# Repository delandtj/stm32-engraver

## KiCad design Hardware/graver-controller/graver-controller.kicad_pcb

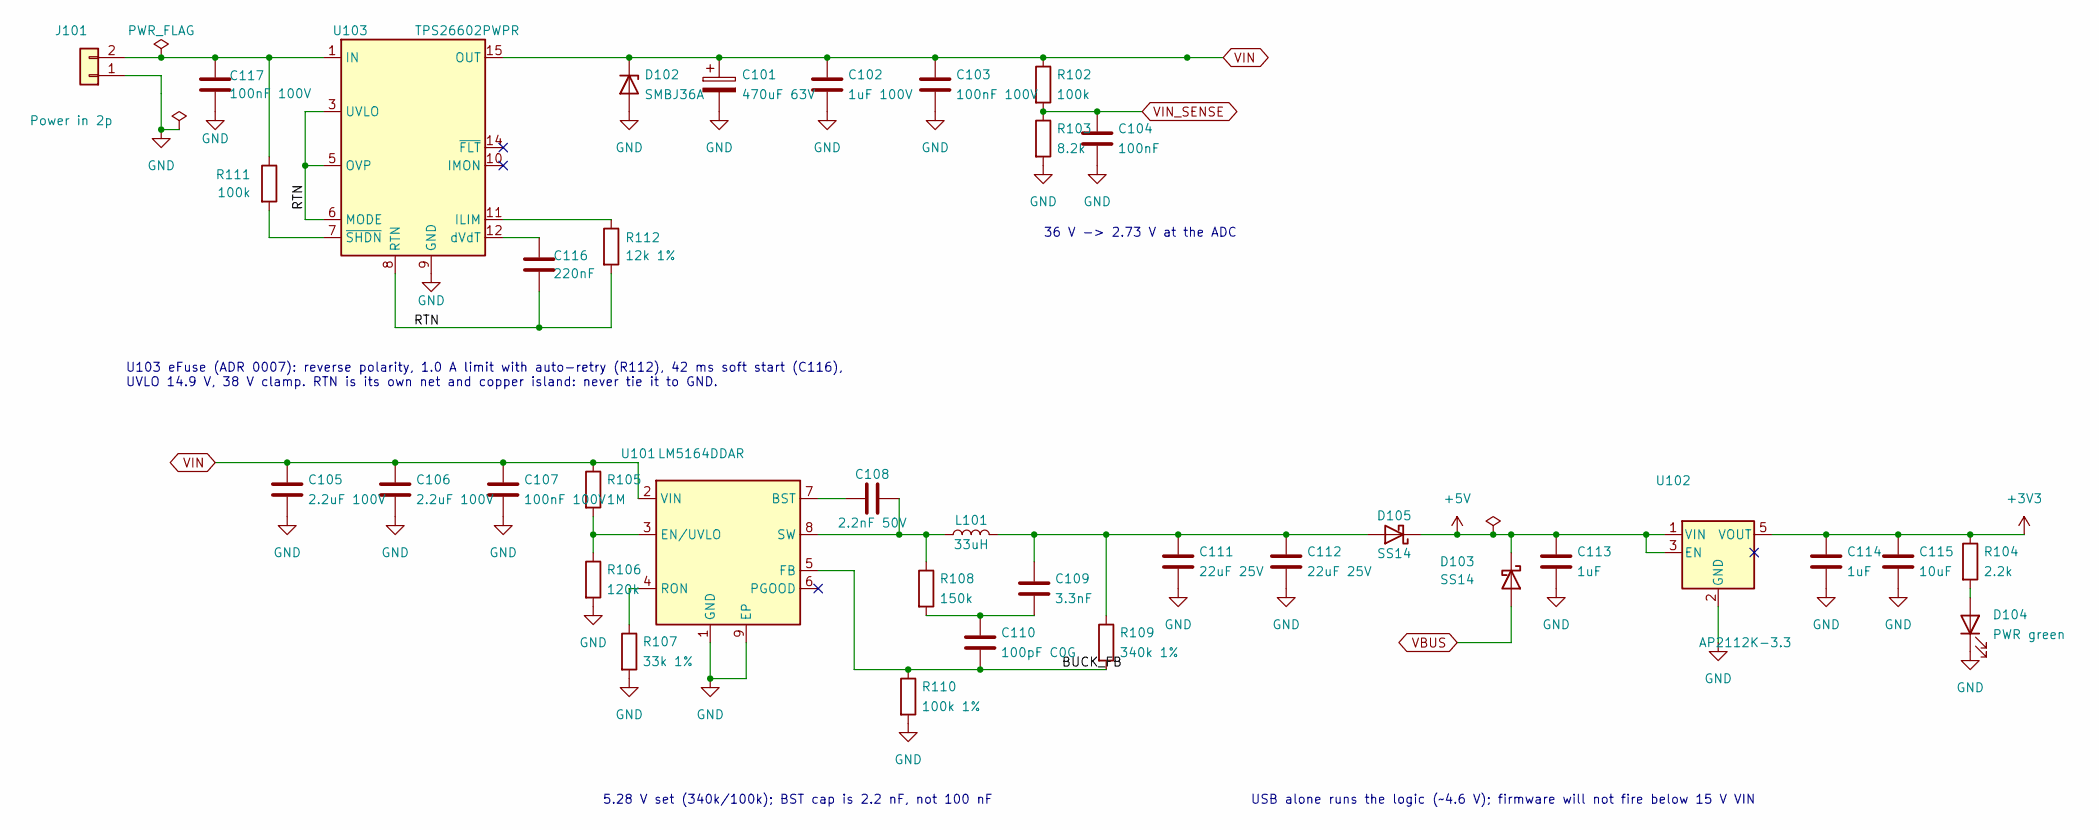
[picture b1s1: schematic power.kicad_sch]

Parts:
C101: 470uF 63V; CP_Radial_D12.5mm_P5.00mm; MPN 63ZLJ470M12.5X20; LCSC C2940725
C102: 1uF 100V; C_0805_2012Metric; MPN CC0805KKX7R0BB105; LCSC C5370002
C103, C107, C117: 100nF 100V; C_0805_2012Metric; MPN CL21B104KCFNNNE; LCSC C28233
C104: 100nF; C_0603_1608Metric; MPN CC0603KRX7R9BB104; LCSC C14663
C105, C106: 2.2uF 100V; C_1206_3216Metric; MPN CL31B225KCHSNNE; LCSC C170101
C108: 2.2nF 50V; C_0603_1608Metric; MPN CL10B222KB8NNNC; LCSC C1604
C109: 3.3nF; C_0603_1608Metric; MPN CL10B332KB8NNNC; LCSC C1613
C110: 100pF C0G; C_0603_1608Metric; MPN CL10C101JB8NNNC; LCSC C14858
C111, C112: 22uF 25V; C_0805_2012Metric; MPN CL21A226MAQNNNE; LCSC C45783
C113, C114: 1uF; C_0603_1608Metric; MPN CL10A105KB8NNNC; LCSC C15849
C115: 10uF; C_0805_2012Metric; MPN CL21A106KAYNNNE; LCSC C15850
C116: 220nF; C_0603_1608Metric; MPN CL10B224KA8NNNC; LCSC C21120
D102: SMBJ36A; D_SMB; MPN SMBJ36A; LCSC C19077588
D103, D105: SS14; D_SMA; MPN SS14; LCSC C2480
D104: PWR green; LED_0805_2012Metric; MPN KT-0805G; LCSC C2297
J101: Power in 2p; SolderWire-1sqmm_1x02_P5.4mm_D1.4mm_OD2.7mm
L101: 33uH; L_Changjiang_FXL0630; MPN FXL0630-330-M; LCSC C177245
R102, R111: 100k; R_0603_1608Metric; MPN 0603WAF1003T5E; LCSC C25803
R103: 8.2k; R_0603_1608Metric; MPN 0603WAF8201T5E; LCSC C25981
R104: 2.2k; R_0603_1608Metric; MPN 0603WAF2201T5E; LCSC C4190
R105: 1M; R_0603_1608Metric; MPN 0603WAF1004T5E; LCSC C22935
R106: 120k; R_0603_1608Metric; MPN 0603WAF1203T5E; LCSC C25808
R107: 33k 1%; R_0603_1608Metric; MPN 0603WAF3302T5E; LCSC C4216
R108: 150k; R_0603_1608Metric; MPN 0603WAF1503T5E; LCSC C22807
R109: 340k 1%; R_0603_1608Metric; MPN FRC0603F3403TS; LCSC C2933203
R110: 100k 1%; R_0603_1608Metric; MPN 0603WAF1003T5E; LCSC C25803
R112: 12k 1%; R_0603_1608Metric; MPN 0603WAF1202T5E; LCSC C22790
U101: LM5164DDAR; HSOP-8-1EP_3.9x4.9mm_P1.27mm_EP2.41x3.1mm; MPN LM5164DDAR; LCSC C477928
U102: AP2112K-3.3; SOT-23-5; MPN AP2112K-3.3TRG1; LCSC C51118
U103: TPS26602PWPR; HTSSOP-16-1EP_4.4x5mm_P0.65mm_EP3.4x5mm_Mask3x3mm_ThermalVi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; MPN TPS26602PWPR; LCSC C2872872

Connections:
+3V3: C114.1, C115.1, R104.1, U102.5 (VOUT); also elsewhere on the board
/Power/BUCK_FB: C110.2, R109.2, R110.1, U101.5 (FB)
/Power/RTN: C116.2, R112.2, U103.3 (UVLO), U103.5 (OVP), U103.6 (MODE), U103.8 (RTN), U103.17 (RTN)
unnamed: C109.1, C110.1, R108.2
unnamed: D104.2 (A), R104.2
unnamed: C109.2, C111.1, C112.1, D105.2 (A), L101.2, R109.1
unnamed: C108.1, U101.7 (BST)
unnamed: R105.2, R106.1, U101.3 (EN/UVLO)
unnamed: R107.1, U101.4 (RON)
unnamed: C108.2, L101.1, R108.1, U101.8 (SW)
unnamed: R112.1, U103.11 (ILIM)
unnamed: C116.1, U103.12 (dVdT)
unnamed: R111.2, U103.7 (~SHDN)
VBUS: D103.2 (A); also elsewhere on the board
VIN: C101.1, C102.1, C103.1, C105.1, C106.1, C107.1, D102.1 (K), R102.1, R105.1, U101.2 (VIN), U103.15 (OUT), U103.16 (OUT); also elsewhere on the board
VIN_SENSE: C104.1, R102.2, R103.1; also elsewhere on the board

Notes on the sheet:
36 V -> 2.73 V at the ADC
5.28 V set (340k/100k); BST cap is 2.2 nF, not 100 nF
USB alone runs the logic (~4.6 V); firmware will not fire below 15 V VIN
U103 eFuse (ADR 0007): reverse polarity, 1.0 A limit with auto-retry (R112), 42 ms soft start (C116), UVLO 14.9 V, 38 V clamp. RTN is its own net and copper island: never tie it to GND.

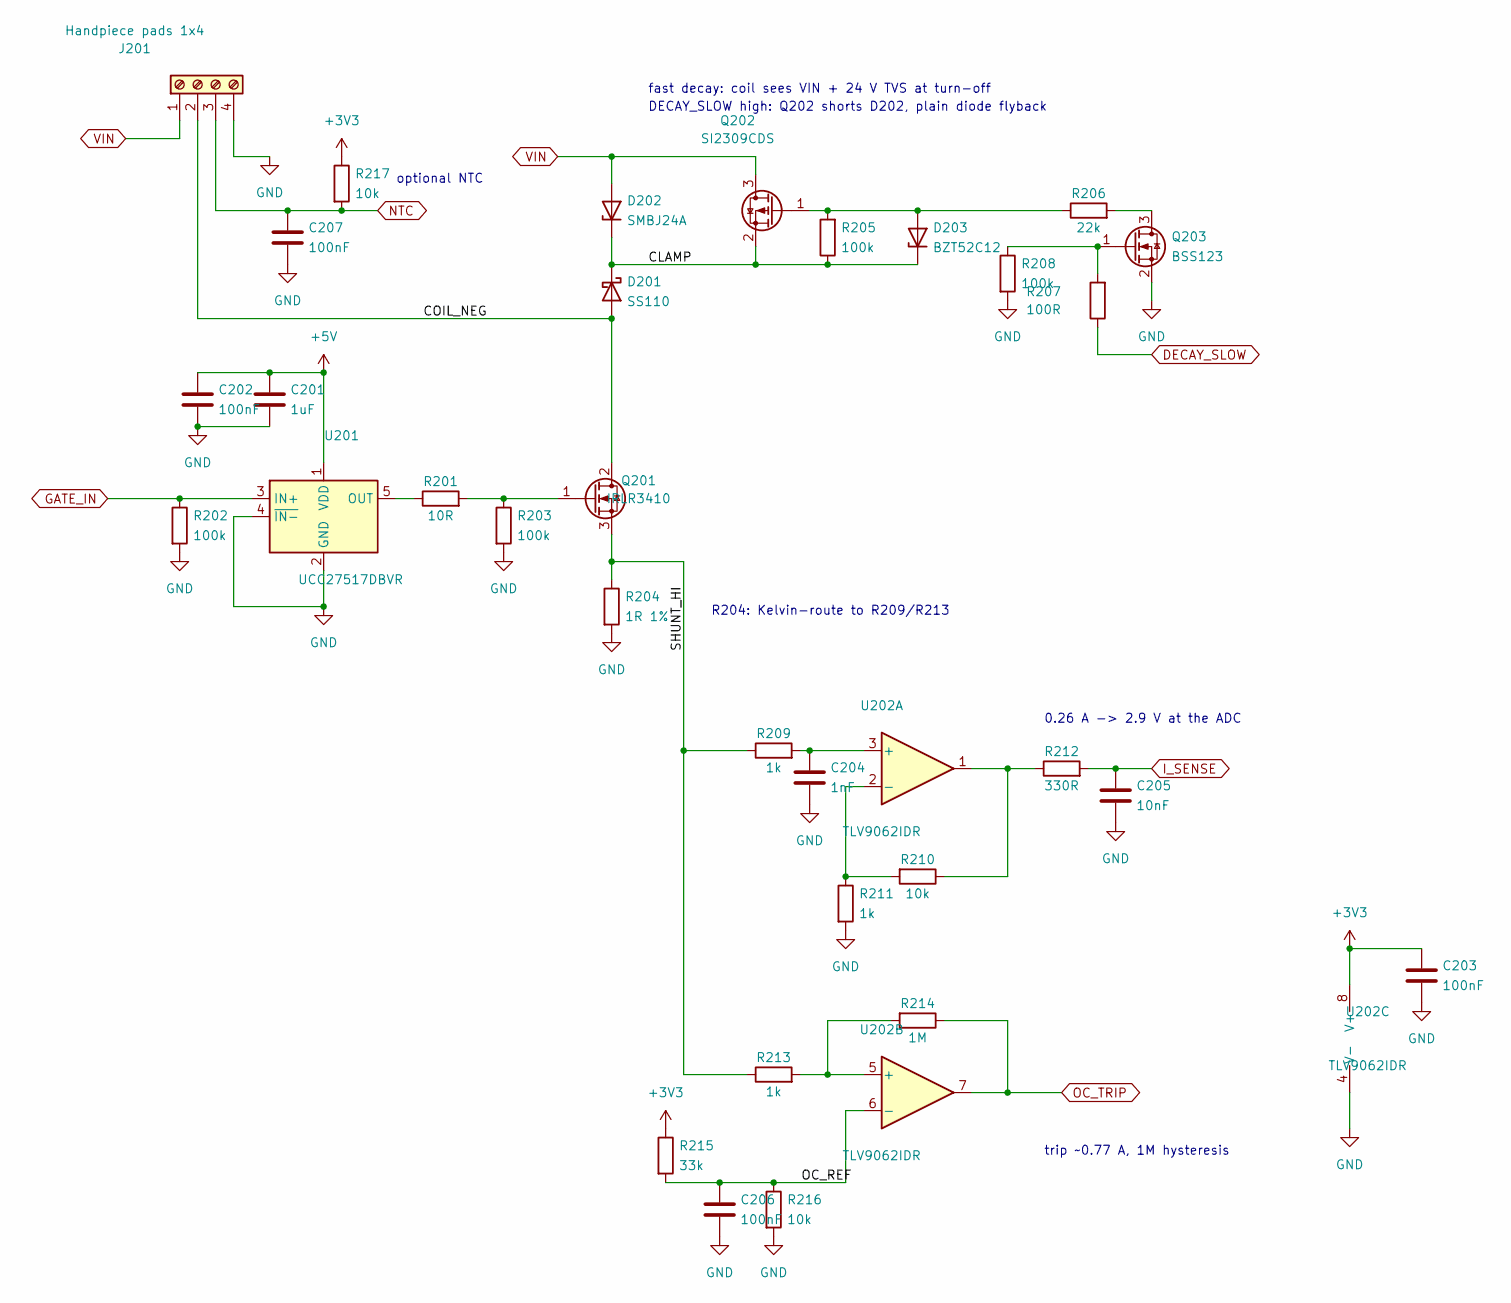
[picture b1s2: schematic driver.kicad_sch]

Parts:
C201: 1uF; C_0603_1608Metric; MPN CL10A105KB8NNNC; LCSC C15849
C202, C203, C206, C207: 100nF; C_0603_1608Metric; MPN CC0603KRX7R9BB104; LCSC C14663
C204: 1nF; C_0603_1608Metric; MPN CL10B102KB8NNNC; LCSC C1588
C205: 10nF; C_0603_1608Metric; MPN CL10B103KB8NNNC; LCSC C57112
D201: SS110; D_SMA; MPN SS110; LCSC C18199178
D202: SMBJ24A; D_SMB; MPN SMBJ24A; LCSC C19077578
D203: BZT52C12; D_SOD-123; MPN BZT52C12; LCSC C19077410
J201: Handpiece pads 1x4; PinHeader_1x04_P2.54mm_Vertical
Q201: IRLR3410; TO-252-2; MPN IRLR3410TRPBF; LCSC C3017
Q202: SI2309CDS; SOT-23; MPN SI2309CDS-T1-GE3; LCSC C10493
Q203: BSS123; SOT-23; MPN BSS123; LCSC C427379
R201: 10R; R_0603_1608Metric; MPN 0603WAF100JT5E; LCSC C22859
R202, R203, R205, R208: 100k; R_0603_1608Metric; MPN 0603WAF1003T5E; LCSC C25803
R204: 1R 1%; R_1206_3216Metric; MPN FRC1206F1R00TS; LCSC C2907374
R206: 22k; R_0603_1608Metric; MPN 0603WAF2202T5E; LCSC C31850
R207: 100R; R_0603_1608Metric; MPN 0603WAF1000T5E; LCSC C22775
R209, R211, R213: 1k; R_0603_1608Metric; MPN 0603WAF1001T5E; LCSC C21190
R210, R216, R217: 10k; R_0603_1608Metric; MPN 0603WAF1002T5E; LCSC C25804
R212: 330R; R_0603_1608Metric; MPN 0603WAF3300T5E; LCSC C23138
R214: 1M; R_0603_1608Metric; MPN 0603WAF1004T5E; LCSC C22935
R215: 33k; R_0603_1608Metric; MPN 0603WAF3302T5E; LCSC C4216
U201: UCC27517DBVR; SOT-23-5; MPN UCC27517DBVR; LCSC C99395
U202: TLV9062IDR; SOIC-8_3.9x4.9mm_P1.27mm; MPN TLV9062IDR; LCSC C398355

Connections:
+3V3: C203.1, R215.1, R217.1, U202.8 (V+); also elsewhere on the board
/Driver/CLAMP: D201.1 (K), D202.1 (K), D203.1 (K), Q202.2 (S), R205.1
/Driver/COIL_NEG: D201.2 (A), J201.2, Q201.2 (D)
/Driver/OC_REF: C206.1, R215.2, R216.1, U202.6 (-)
/Driver/SHUNT_HI: Q201.3 (S), R204.1, R209.1, R213.1
DECAY_SLOW: R207.1; also elsewhere on the board
GATE_IN: R202.1, U201.3 (IN+); also elsewhere on the board
I_SENSE: C205.1, R212.2; also elsewhere on the board
NTC: C207.1, J201.3, R217.2; also elsewhere on the board
unnamed: D203.2 (A), Q202.1 (G), R205.2, R206.1
unnamed: Q201.1 (G), R201.2, R203.1
unnamed: Q203.3 (D), R206.2
unnamed: Q203.1 (G), R207.2, R208.1
unnamed: R210.1, R212.1, U202.1
unnamed: R201.1, U201.5 (OUT)
unnamed: C204.1, R209.2, U202.3 (+)
unnamed: R210.2, R211.1, U202.2 (-)
unnamed: R213.2, R214.2, U202.5 (+)
OC_TRIP: R214.1, U202.7; also elsewhere on the board
VIN: D202.2 (A), J201.1, Q202.3 (D); also elsewhere on the board

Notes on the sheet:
optional NTC
trip ~0.77 A, 1M hysteresis
R204: Kelvin-route to R209/R213
fast decay: coil sees VIN + 24 V TVS at turn-off
0.26 A -> 2.9 V at the ADC
DECAY_SLOW high: Q202 shorts D202, plain diode flyback

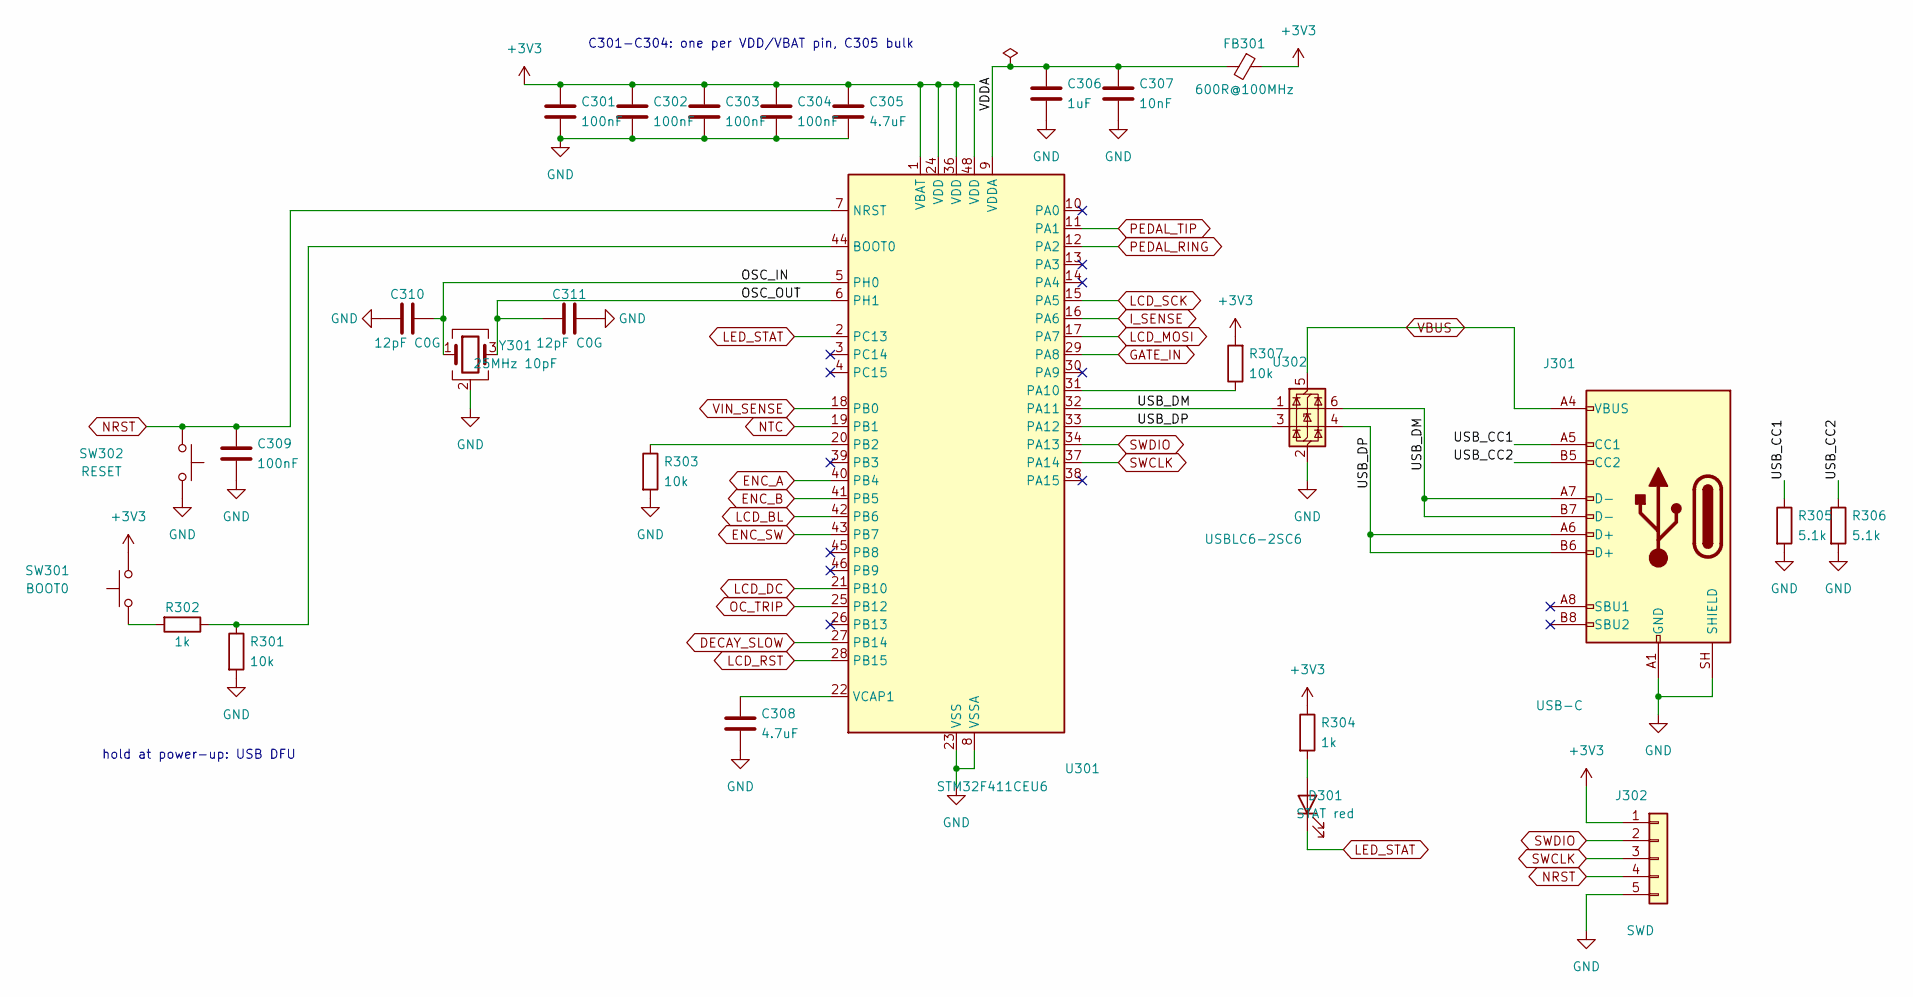
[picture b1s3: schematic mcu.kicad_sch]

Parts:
C301, C302, C303, C304, C309: 100nF; C_0603_1608Metric; MPN CC0603KRX7R9BB104; LCSC C14663
C305, C308: 4.7uF; C_0603_1608Metric; MPN CL10A475KO8NNNC; LCSC C19666
C306: 1uF; C_0603_1608Metric; MPN CL10A105KB8NNNC; LCSC C15849
C307: 10nF; C_0603_1608Metric; MPN 0603B103K500NT; LCSC C57112
C310, C311: 12pF C0G; C_0402_1005Metric; MPN 0402CG120J500NT; LCSC C1547
D301: STAT red; LED_0603_1608Metric; MPN KT-0603R; LCSC C2286
FB301: 600R@100MHz; L_0603_1608Metric; MPN GZ1608D601TF; LCSC C1002
J301: USB-C; USB_C_Receptacle_HRO_TYPE-C-31-M-12; MPN TYPE-C-31-M-12; LCSC C165948
J302: SWD; PinHeader_1x05_P2.54mm_Vertical; MPN PZ254V-11-05P; LCSC C492404
R301, R303, R307: 10k; R_0603_1608Metric; MPN 0603WAF1002T5E; LCSC C25804
R302, R304: 1k; R_0603_1608Metric; MPN 0603WAF1001T5E; LCSC C21190
R305, R306: 5.1k; R_0603_1608Metric; MPN 0603WAF5101T5E; LCSC C23186
SW301: BOOT0; SW_Push_1P1T_XKB_TS-1187A; MPN TS-1187A-B-A-B; LCSC C318884
SW302: RESET; SW_Push_1P1T_XKB_TS-1187A; MPN TS-1187A-B-A-B; LCSC C318884
U301: STM32F411CEU6; QFN-48-1EP_7x7mm_P0.5mm_EP5.6x5.6mm; MPN STM32F411CEU6; LCSC C60420
U302: USBLC6-2SC6; SOT-23-6; MPN USBLC6-2SC6; LCSC C7519
Y301: 25MHz 10pF; Crystal_SMD_3225-4Pin_3.2x2.5mm; MPN X322525MMB4SI; LCSC C70582

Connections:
+3V3: C301.1, C302.1, C303.1, C304.1, C305.1, FB301.1, J302.1, R304.1, R307.2, SW301.2, U301.1 (VBAT), U301.24 (VDD), U301.36 (VDD), U301.48 (VDD); also elsewhere on the board
/MCU/OSC_IN: C310.1, U301.5 (PH0), Y301.1
/MCU/OSC_OUT: C311.1, U301.6 (PH1), Y301.3
/MCU/USB_CC1: J301.A5 (CC1), R305.1
/MCU/USB_CC2: J301.B5 (CC2), R306.1
/MCU/USB_DM: J301.A7 (D-), J301.B7 (D-), U301.32 (PA11), U302.1 (I/O1), U302.6 (I/O1)
/MCU/USB_DP: J301.A6 (D+), J301.B6 (D+), U301.33 (PA12), U302.3 (I/O2), U302.4 (I/O2)
/MCU/VDDA: C306.1, C307.1, FB301.2, U301.9 (VDDA)
DECAY_SLOW: U301.27 (PB14); also elsewhere on the board
ENC_A: U301.40 (PB4); also elsewhere on the board
ENC_B: U301.41 (PB5); also elsewhere on the board
ENC_SW: U301.43 (PB7); also elsewhere on the board
GATE_IN: U301.29 (PA8); also elsewhere on the board
I_SENSE: U301.16 (PA6); also elsewhere on the board
LCD_BL: U301.42 (PB6); also elsewhere on the board
LCD_DC: U301.21 (PB10); also elsewhere on the board
LCD_MOSI: U301.17 (PA7); also elsewhere on the board
LCD_RST: U301.28 (PB15); also elsewhere on the board
LCD_SCK: U301.15 (PA5); also elsewhere on the board
LED_STAT: D301.1 (K), U301.2 (PC13)
NRST: C309.1, J302.4, SW302.1, U301.7 (NRST)
NTC: U301.19 (PB1); also elsewhere on the board
unnamed: D301.2 (A), R304.2
unnamed: R302.2, SW301.1
unnamed: R301.1, R302.1, U301.44 (BOOT0)
unnamed: R307.1, U301.31 (PA10)
unnamed: R303.1, U301.20 (PB2)
unnamed: C308.1, U301.22 (VCAP1)
OC_TRIP: U301.25 (PB12); also elsewhere on the board
PEDAL_RING: U301.12 (PA2); also elsewhere on the board
PEDAL_TIP: U301.11 (PA1); also elsewhere on the board
SWCLK: J302.3, U301.37 (PA14)
SWDIO: J302.2, U301.34 (PA13)
VBUS: J301.A4 (VBUS), J301.A9 (VBUS), J301.B4 (VBUS), J301.B9 (VBUS), U302.5 (VBUS); also elsewhere on the board
VIN_SENSE: U301.18 (PB0); also elsewhere on the board

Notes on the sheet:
hold at power-up: USB DFU
C301-C304: one per VDD/VBAT pin, C305 bulk

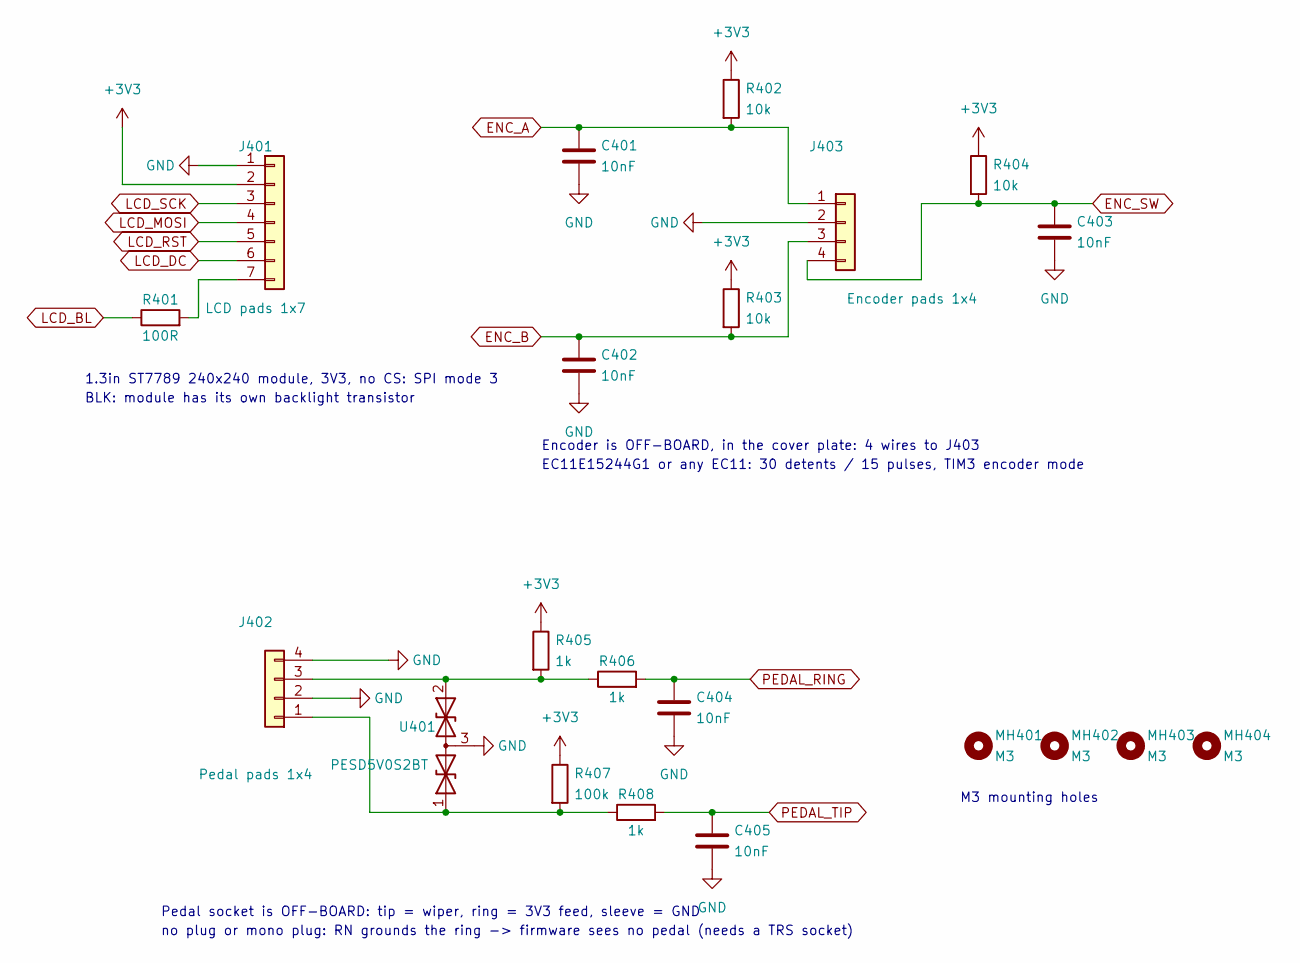
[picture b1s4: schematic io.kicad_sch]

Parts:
C401, C402, C403, C404, C405: 10nF; C_0603_1608Metric; MPN 0603B103K500NT; LCSC C57112
J401: LCD pads 1x7; PinHeader_1x07_P2.54mm_Vertical
J402: Pedal pads 1x4; PinHeader_1x04_P2.54mm_Vertical
J403: Encoder pads 1x4; PinHeader_1x04_P2.54mm_Vertical
MH401, MH402, MH403, MH404: M3; MountingHole_3.2mm_M3
R401: 100R; R_0603_1608Metric; MPN 0603WAF1000T5E; LCSC C22775
R402, R403, R404: 10k; R_0402_1005Metric; MPN 0402WGF1002TCE; LCSC C25744
R405, R406, R408: 1k; R_0603_1608Metric; MPN 0603WAF1001T5E; LCSC C21190
R407: 100k; R_0603_1608Metric; MPN 0603WAF1003T5E; LCSC C25803
U401: PESD5V0S2BT; SOT-23; MPN PESD5V0S2BT,215; LCSC C49338

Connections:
+3V3: J401.2, R402.1, R403.1, R404.1, R405.1, R407.1; also elsewhere on the board
ENC_A: C401.1, J403.1, R402.2; also elsewhere on the board
ENC_B: C402.1, J403.3, R403.2; also elsewhere on the board
ENC_SW: C403.1, J403.4, R404.2; also elsewhere on the board
LCD_BL: R401.1; also elsewhere on the board
LCD_DC: J401.6; also elsewhere on the board
LCD_MOSI: J401.4; also elsewhere on the board
LCD_RST: J401.5; also elsewhere on the board
LCD_SCK: J401.3; also elsewhere on the board
unnamed: J401.7, R401.2
unnamed: J402.1, R407.2, R408.1, U401.1 (A1)
unnamed: J402.3, R405.2, R406.1, U401.2 (A2)
PEDAL_RING: C404.1, R406.2; also elsewhere on the board
PEDAL_TIP: C405.1, R408.2; also elsewhere on the board

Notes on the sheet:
no plug or mono plug: RN grounds the ring -> firmware sees no pedal (needs a TRS socket)
Encoder is OFF-BOARD, in the cover plate: 4 wires to J403
EC11E15244G1 or any EC11: 30 detents / 15 pulses, TIM3 encoder mode
1.3in ST7789 240x240 module, 3V3, no CS: SPI mode 3
BLK: module has its own backlight transistor
M3 mounting holes
Pedal socket is OFF-BOARD: tip = wiper, ring = 3V3 feed, sleeve = GND

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
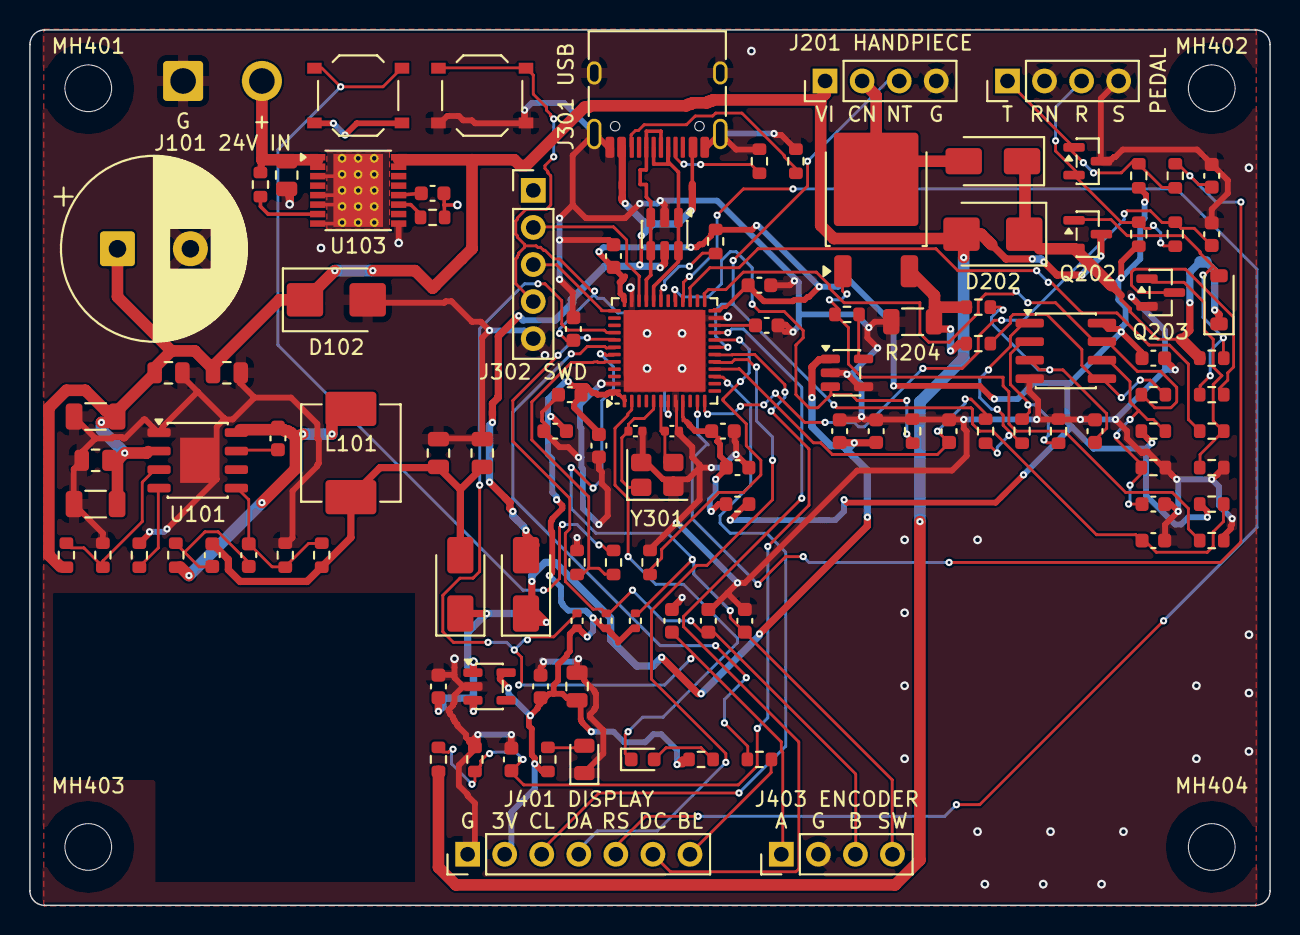
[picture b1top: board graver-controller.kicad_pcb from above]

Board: 4 copper layers, 85.0 x 60.0 mm, 118 parts (0 on the bottom side), 67 nets.

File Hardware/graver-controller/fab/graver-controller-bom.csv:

"Comment","Designator","Footprint","LCSC Part #"
"470uF 63V","C101","CP_Radial_D12.5mm_P5.00mm","C2940725"
"1uF 100V","C102","C_0805_2012Metric","C5370002"
"100nF 100V","C103,C107","C_0805_2012Metric","C28233"
"100nF","C104,C202,C203,C206,C207,C301,C302,C303,C304,C309","C_0603_1608Metric","C14663"
"2.2uF 100V","C105,C106","C_1206_3216Metric","C170101"
"2.2nF 50V","C108","C_0603_1608Metric","C1604"
"3.3nF","C109","C_0603_1608Metric","C1613"
"100pF C0G","C110","C_0603_1608Metric","C14858"
"22uF 25V","C111,C112","C_0805_2012Metric","C45783"
"1uF","C113,C114,C201,C306","C_0603_1608Metric","C15849"
"10uF","C115","C_0805_2012Metric","C15850"
"1nF","C204","C_0603_1608Metric","C1588"
"10nF","C205,C307,C401,C402,C403,C404,C405","C_0603_1608Metric","C57112"
"4.7uF","C305,C308","C_0603_1608Metric","C19666"
"12pF C0G","C310,C311","C_0402_1005Metric","C1547"
"BZT52C12","D101,D203","D_SOD-123","C19077410"
"SMBJ36A","D102","D_SMB","C19077588"
"SS14","D103,D105","D_SMA","C2480"
"PWR green","D104","LED_0805_2012Metric","C2297"
"SS110","D201","D_SMA","C18199178"
"SMBJ24A","D202","D_SMB","C19077578"
"STAT red","D301","LED_0603_1608Metric","C2286"
"1A slow","F101","Fuse_1206_3216Metric","C99537"
"600R@100MHz","FB301","L_0603_1608Metric","C1002"
"USB-C","J301","USB_C_Receptacle_HRO_TYPE-C-31-M-12","C165948"
"SWD","J302","PinHeader_1x05_P2.54mm_Vertical","C492404"
"33uH","L101","L_Changjiang_FXL0630","C177245"
"DMP6023LE","Q101","SOT-223-3_TabPin2","C154901"
"IRLR3410","Q201","TO-252-2","C3017"
"SI2309CDS","Q202","SOT-23","C10493"
"BSS123","Q203","SOT-23","C427379"
"0603WAF1003T5E","R101,R102,R110,R202,R203,R205,R208,R407","R_0603_1608Metric","C25803"
"8.2k","R103","R_0603_1608Metric","C25981"
"2.2k","R104","R_0603_1608Metric","C4190"
"1M","R105,R214","R_0603_1608Metric","C22935"
"120k","R106","R_0603_1608Metric","C25808"
"0603WAF3302T5E","R107,R215","R_0603_1608Metric","C4216"
"150k","R108","R_0603_1608Metric","C22807"
"340k 1%","R109","R_0603_1608Metric","C2933203"
"10R","R201","R_0603_1608Metric","C22859"
"1R 1%","R204","R_1206_3216Metric","C2907374"
"22k","R206","R_0603_1608Metric","C31850"
"100R","R207,R401","R_0603_1608Metric","C22775"
"1k","R209,R211,R213,R302,R304,R405,R406,R408","R_0603_1608Metric","C21190"
"10k","R210,R216,R217,R301,R303,R307","R_0603_1608Metric","C25804"
"330R","R212","R_0603_1608Metric","C23138"
"5.1k","R305,R306","R_0603_1608Metric","C23186"
"10k","R402,R403,R404","R_0402_1005Metric","C25744"
"TS-1187A-B-A-B","SW301,SW302","SW_Push_1P1T_XKB_TS-1187A","C318884"
"LM5164DDAR","U101","HSOP-8-1EP_3.9x4.9mm_P1.27mm_EP2.41x3.1mm","C477928"
"AP2112K-3.3","U102","SOT-23-5","C51118"
"UCC27517DBVR","U201","SOT-23-5","C99395"
"TLV9062IDR","U202","SOIC-8_3.9x4.9mm_P1.27mm","C398355"
"STM32F411CEU6","U301","QFN-48-1EP_7x7mm_P0.5mm_EP5.6x5.6mm","C60420"
"USBLC6-2SC6","U302","SOT-23-6","C7519"
"PESD5V0S2BT","U401","SOT-23","C49338"
"25MHz 10pF","Y301","Crystal_SMD_3225-4Pin_3.2x2.5mm","C70582"
